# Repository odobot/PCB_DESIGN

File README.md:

# HALLO EYE

# LORA GATEWAY

# LORA TRACKER

# PENTASLAM BOARD V2
### Fixed issue of overheating that occured in V1.

# VEHICLE TELEMATICS

# PENTASLAM BOARD
### https://oshwlab.com/ndibapeter4/hexapod

# HEXAPOD BOARD
### https://oshwlab.com/ndibapeter4/hexapod

# SWIMMING-POOL-REGULATOR
### https://oshwlab.com/ndibapeter4/wsa-pcb

# CO2_SENSOR_BOARD

# NFC-READER FOR A TRAIN
### https://oshwlab.com/ndibapeter4/nfc-tag

# MOTOR-KIT BOARD
micro-ros motor control learning kit

24-08-22 at 06 37 44_fead27ea](https://github.com/user-attachments/assets/46265f90-ea3d-4042-9f53-f933ec7b34d7)

# ARDUINO-MEGA CUSTOM BOARD

# GREENHOUSE PCB

# ATMEGA32_ROBOT

# IR-ARRAY
used in line tracking robot

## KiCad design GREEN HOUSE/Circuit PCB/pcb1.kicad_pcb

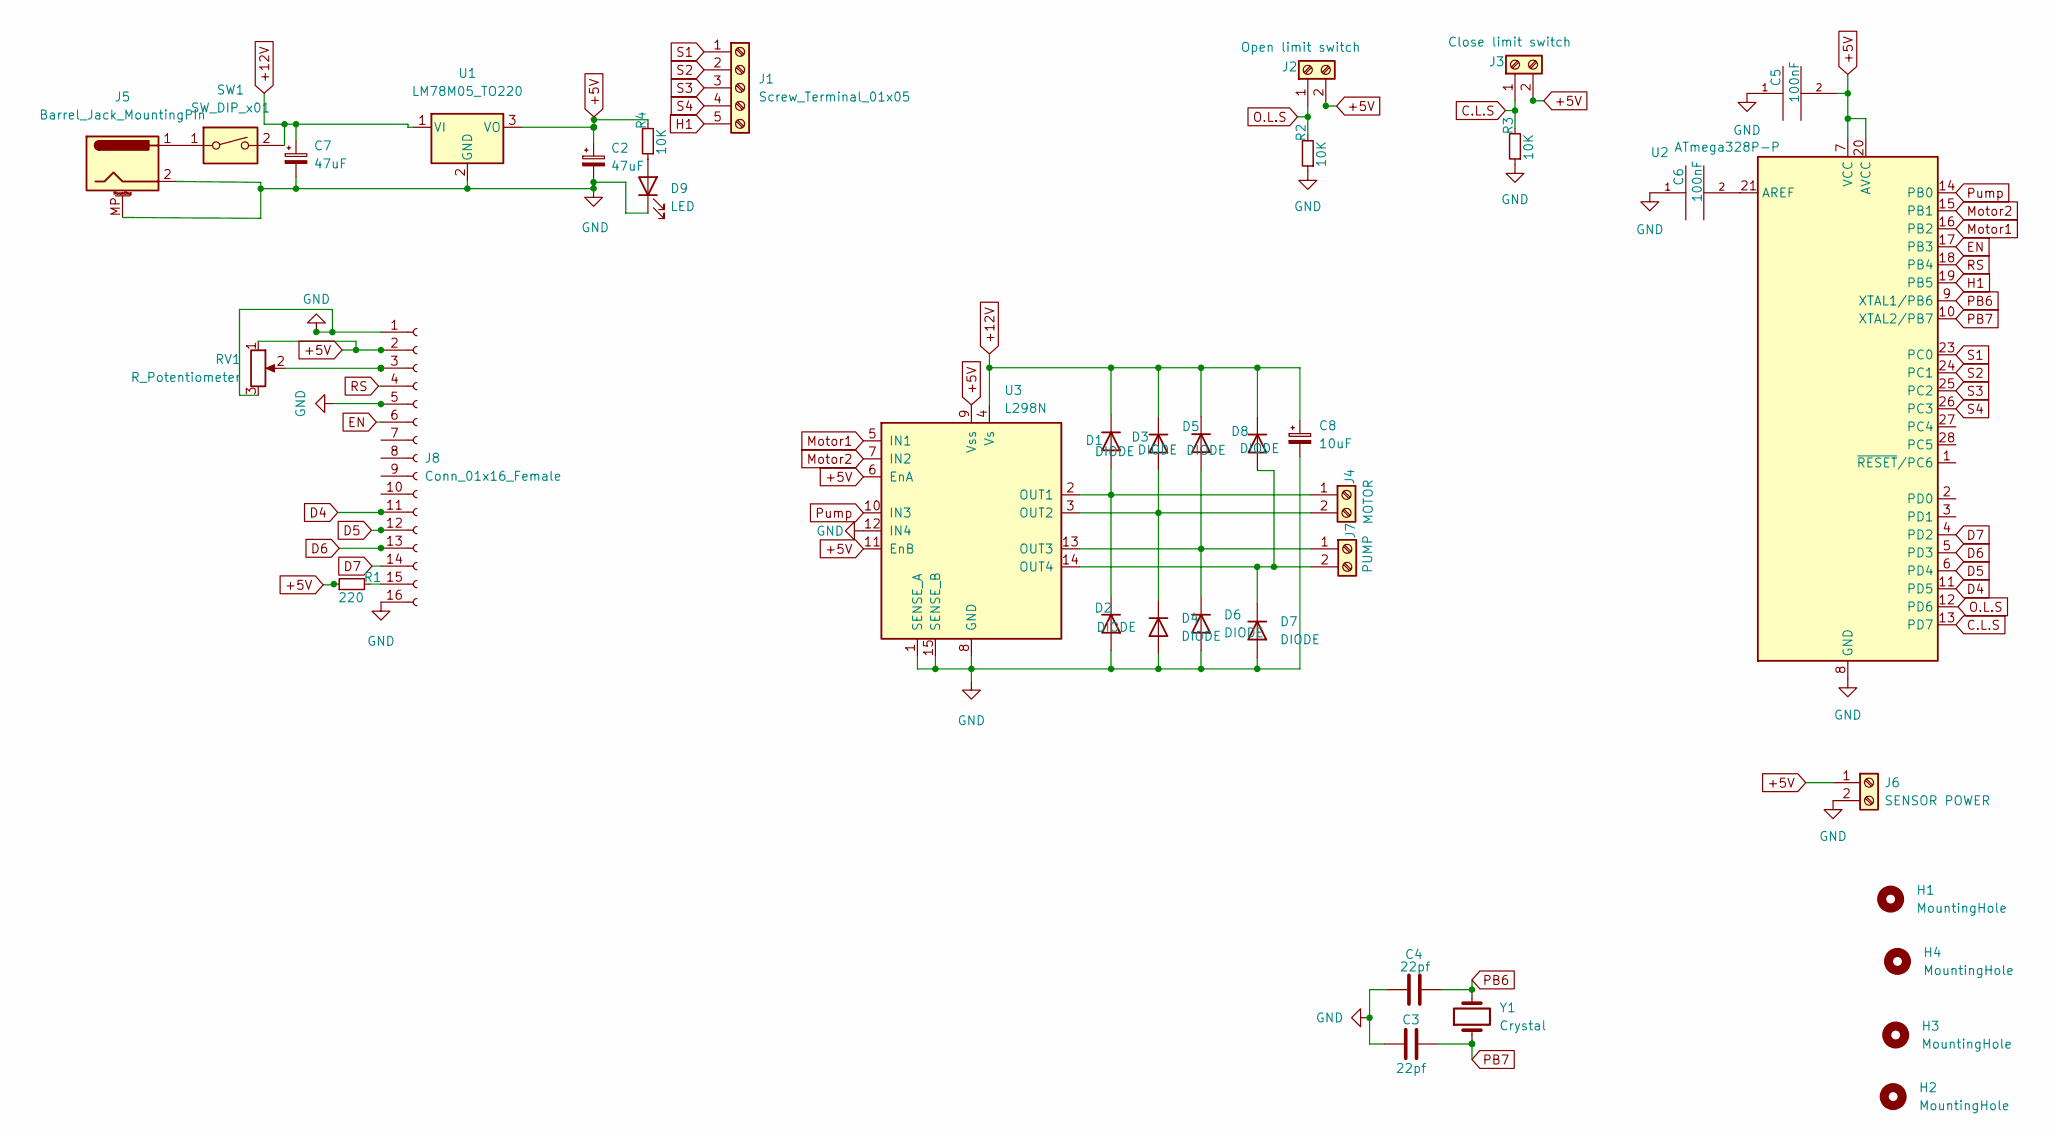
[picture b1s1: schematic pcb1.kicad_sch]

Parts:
C2, C7: 47uF; CP_Radial_D10.0mm_P5.00mm
C3, C4: 22pf; C_Disc_D3.4mm_W2.1mm_P2.50mm
C5, C6: 100nF; C_Disc_D3.0mm_W2.0mm_P2.50mm
C8: 10uF; CP_Radial_D10.0mm_P5.00mm
D1, D2, D3, D4, D5, D6, D7, D8: DIODE; D_A-405_P10.16mm_Horizontal
D9: LED; LED_D5.0mm
H1, H2, H3, H4: MountingHole; MountingHole_2.1mm
J1: Screw_Terminal_01x05; TerminalBlock_Phoenix_MKDS-1,5-5_1x05_P5.00mm_Horizontal
J2: Open limit switch; TerminalBlock_Phoenix_MKDS-1,5-2-5.08_1x02_P5.08mm_Horizont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
J3: Close limit switch; TerminalBlock_Phoenix_MKDS-1,5-2-5.08_1x02_P5.08mm_Horizont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
J4: MOTOR; TerminalBlock_Phoenix_MKDS-1,5-2-5.08_1x02_P5.08mm_Horizont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
J5: Barrel_Jack_MountingPin; BarrelJack_CUI_PJ-063AH_Horizontal
J6: SENSOR POWER; TerminalBlock_Phoenix_MKDS-1,5-2-5.08_1x02_P5.08mm_Horizont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
J7: PUMP; TerminalBlock_Phoenix_MKDS-1,5-2-5.08_1x02_P5.08mm_Horizont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
J8: Conn_01x16_Female; PinSocket_1x16_P2.54mm_Vertical
R1: 220; R_Axial_DIN0516_L15.5mm_D5.0mm_P20.32mm_Horizontal
R2, R3: 10K; R_Axial_DIN0516_L15.5mm_D5.0mm_P20.32mm_Horizontal
R4: 10K; R_Axial_DIN0516_L15.5mm_D5.0mm_P7.62mm_Vertical
RV1: R_Potentiometer; Potentiometer_Bourns_3296W_Vertical
SW1: SW_DIP_x01; SW_CuK_OS102011MA1QN1_SPDT_Angled
U1: LM78M05_TO220; TO-220-3_Vertical
U2: ATmega328P-P; DIP-28_W7.62mm
U3: L298N; TO-220-15_P2.54x2.54mm_StaggerOdd_Lead4.58mm_Vertical
Y1: Crystal; Crystal_HC49-4H_Vertical

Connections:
+5V: C2.1, C5.2, J2.2, J3.2, J6.1, J8.2, R1.1, R4.2, RV1.1, U1.3 (VO), U2.7 (VCC), U2.20 (AVCC), U3.6 (EnA), U3.9 (Vss), U3.11 (EnB)
+12V: C7.1, C8.1, D1.2 (K), D3.2 (K), D5.2 (K), D8.2 (K), SW1.2, U1.1 (VI), U3.4 (Vs)
C.L.S: J3.1, R3.2, U2.13 (PD7)
D4: J8.11, U2.11 (PD5)
D5: J8.12, U2.6 (PD4)
D6: J8.13, U2.5 (PD3)
D7: J8.14, U2.4 (PD2)
EN: J8.6, U2.17 (PB3)
GND: C2.2, C3.1, C4.1, C5.1, C6.1, C7.2, C8.2, D2.1 (A), D4.1 (A), D6.1 (A), D7.1 (A), D9.1 (K), J5.2, J5.MP (MountPin), J6.2, J8.1, J8.5, J8.16, R2.1, R3.1, RV1.3, U1.2 (GND), U2.8 (GND), U2.22 (GND), U3.1 (SENSE_A), U3.8 (GND), U3.12 (IN4), U3.15 (SENSE_B)
H1: J1.5, U2.19 (PB5)
Motor1: U2.16 (PB2), U3.5 (IN1)
Motor2: U2.15 (PB1), U3.7 (IN2)
unnamed: C6.2, U2.21 (AREF)
unnamed: D1.1 (A), D2.2 (K), J4.1, U3.2 (OUT1)
unnamed: D3.1 (A), D4.2 (K), J4.2, U3.3 (OUT2)
unnamed: D5.1 (A), D6.2 (K), J7.1, U3.13 (OUT3)
unnamed: D7.2 (K), D8.1 (A), J7.2, U3.14 (OUT4)
unnamed: D9.2 (A), R4.1
unnamed: J5.1, SW1.1
unnamed: J8.3, RV1.2
unnamed: J8.15, R1.2
O.L.S: J2.1, R2.2, U2.12 (PD6)
PB6: C4.2, U2.9 (XTAL1/PB6), Y1.2
PB7: C3.2, U2.10 (XTAL2/PB7), Y1.1
Pump: U2.14 (PB0), U3.10 (IN3)
RS: J8.4, U2.18 (PB4)
S1: J1.1, U2.23 (PC0)
S2: J1.2, U2.24 (PC1)
S3: J1.3, U2.25 (PC2)
S4: J1.4, U2.26 (PC3)

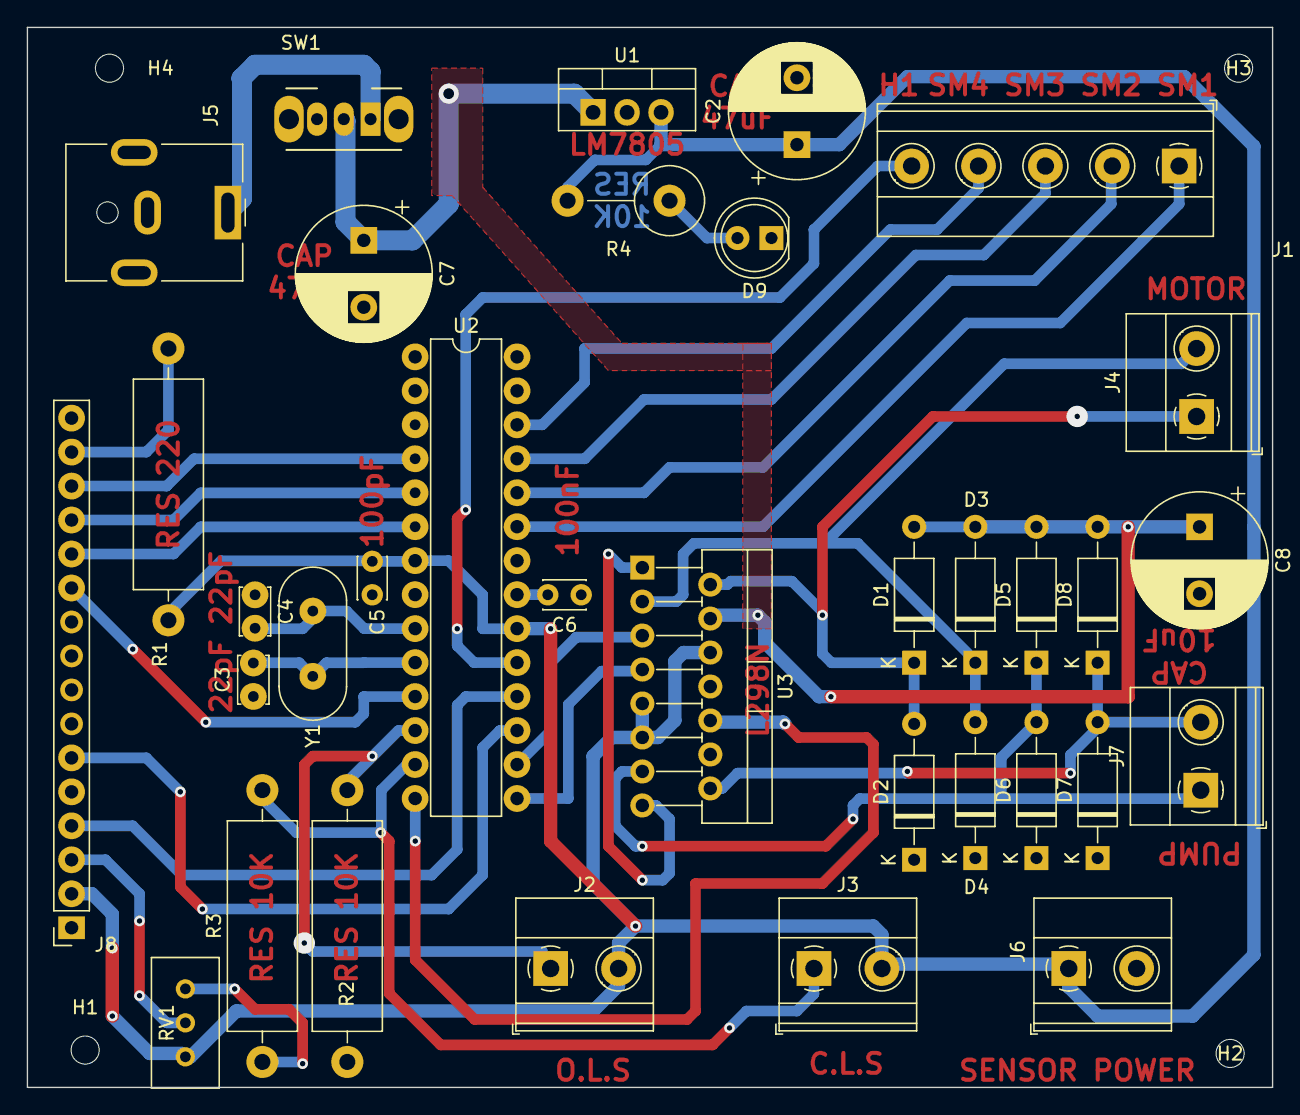
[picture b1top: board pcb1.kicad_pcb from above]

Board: 2 copper layers, 93.1 x 79.2 mm, 38 parts (0 on the bottom side), 30 nets.

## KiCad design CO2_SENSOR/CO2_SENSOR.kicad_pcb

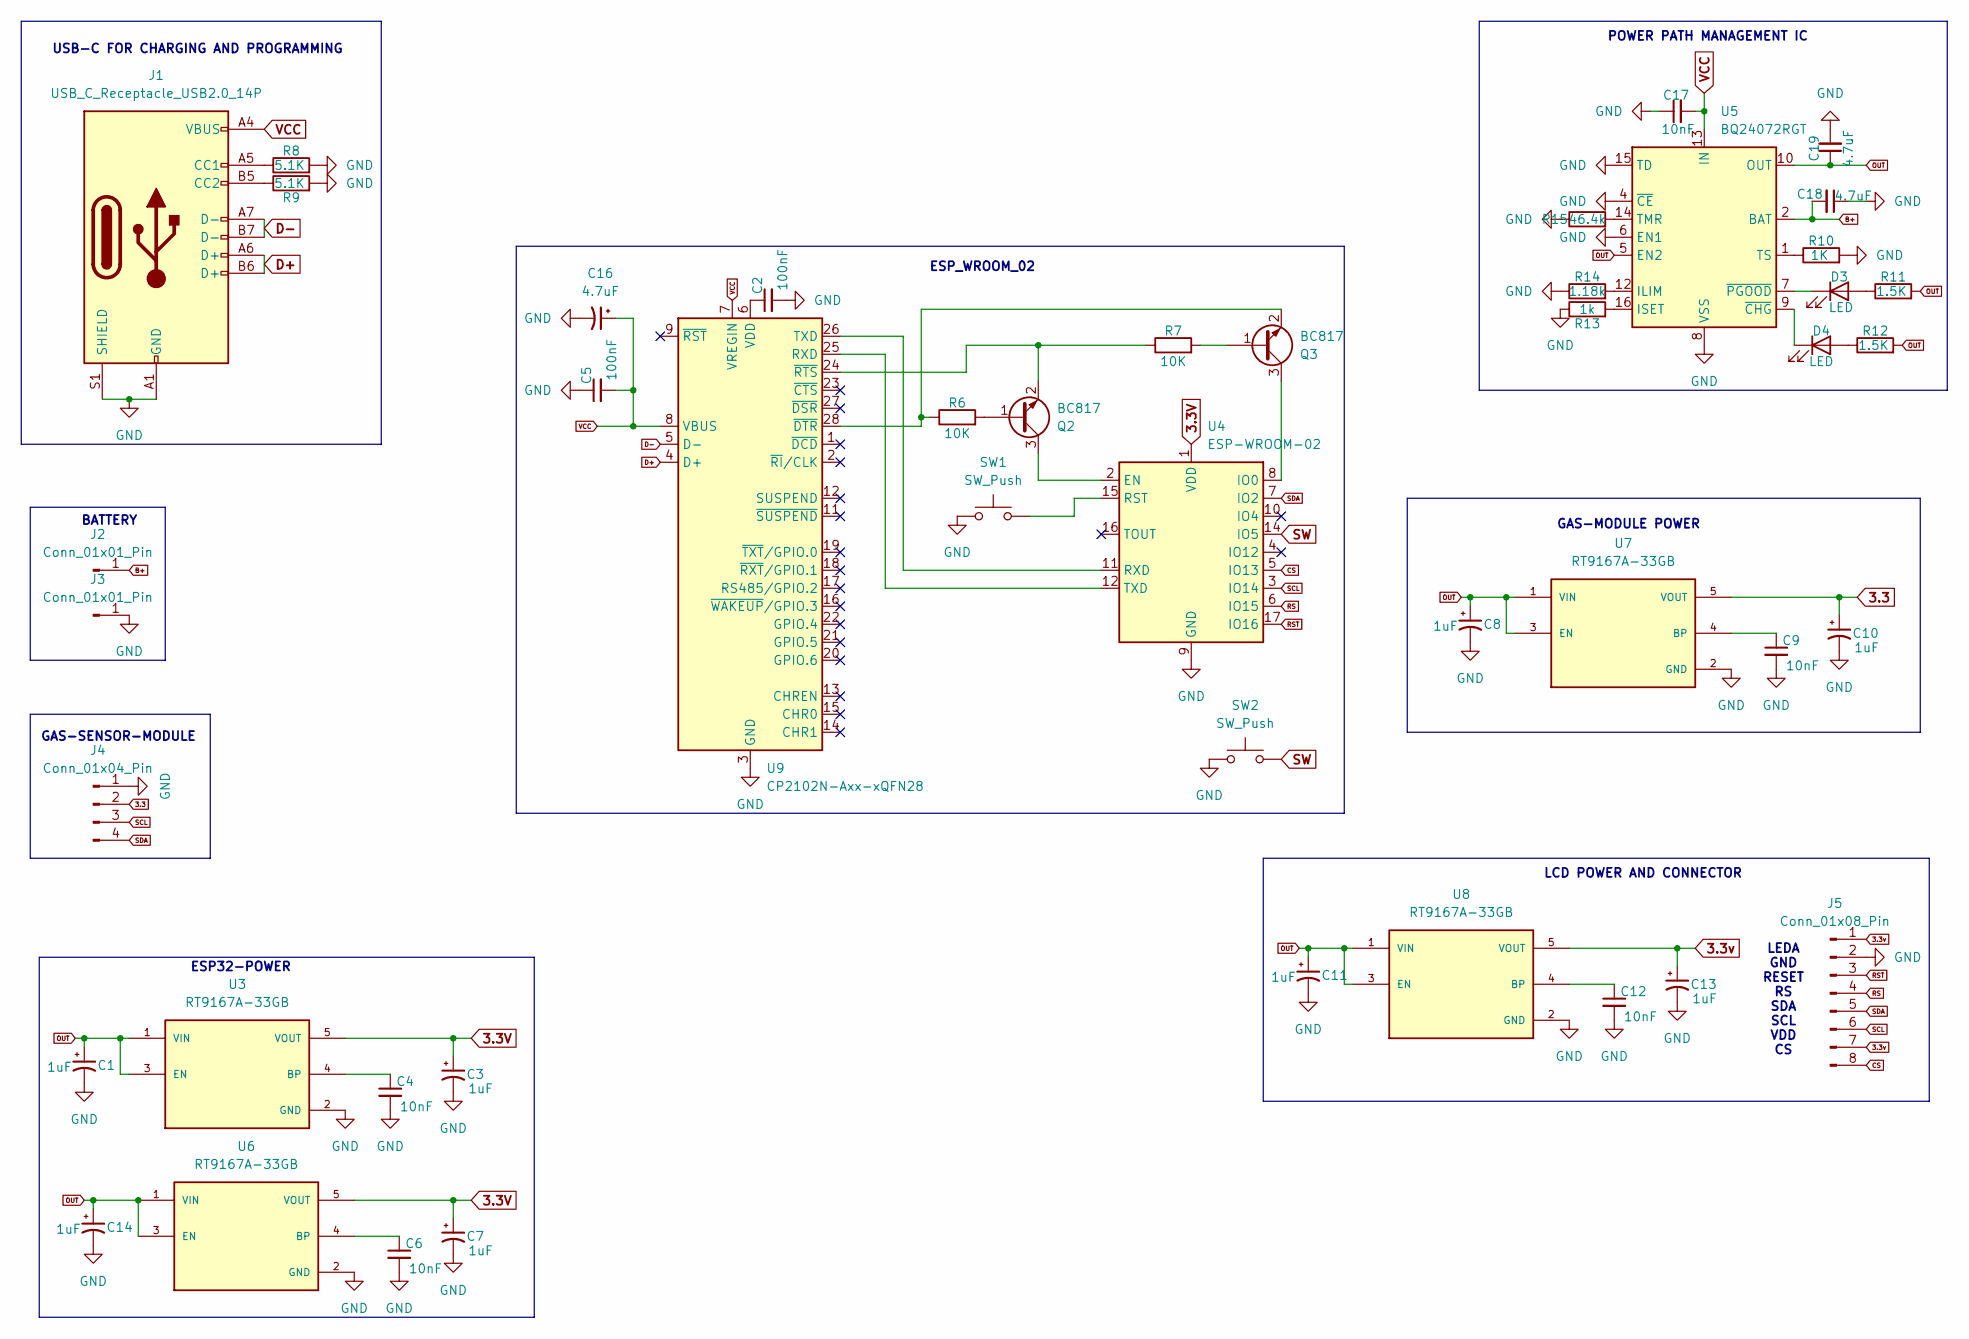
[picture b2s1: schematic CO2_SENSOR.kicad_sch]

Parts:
C1, C3, C7, C8, C10, C11, C13, C14: 1uF; CP_EIA-6032-20_AVX-F_Pad2.25x2.35mm_HandSolder
C2: 100nF; C_0402_1005Metric
C4, C6, C9, C12, C17: 10nF; C_0805_2012Metric
C5: 100nF; C_0603_1608Metric
C16: 4.7uF; CP_EIA-6032-20_AVX-F_Pad2.25x2.35mm_HandSolder
C18, C19: 4.7uF; C_0805_2012Metric
D3, D4: LED; LED_0805_2012Metric
J1: USB_C_Receptacle_USB2.0_14P; USB_C_Receptacle_GCT_USB4105-xx-A_16P_TopMnt_Horizontal
J2, J3: Conn_01x01_Pin; TestPoint_Pad_1.5x1.5mm
J4: Conn_01x04_Pin; PinHeader_1x04_P2.54mm_Vertical
J5: Conn_01x08_Pin; lcd
Q2, Q3: BC817; SOT-23
R6, R7: 10K; R_0805_2012Metric
R8, R9: 5.1K; R_0402_1005Metric
R10: 1K; R_0402_1005Metric
R11, R12: 1.5K; R_0805_2012Metric
R13: 1k; R_0402_1005Metric
R14: 1.18k; R_0402_1005Metric
R15: 46.4k; R_0402_1005Metric
SW1, SW2: SW_Push; SW_Tactile_SPST_NO_Straight_CK_PTS636Sx25SMTRLFS
U3, U6, U7, U8: RT9167A-33GB; SOT94P279X129-5N; PARTREV April 2011
U4: ESP-WROOM-02
U5: BQ24072RGT; VQFN-16-1EP_3x3mm_P0.5mm_EP1.6x1.6mm
U9: CP2102N-Axx-xQFN28; QFN-28-1EP_5x5mm_P0.5mm_EP3.35x3.35mm

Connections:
3.3: C10.1, J4.2, U7.5 (VOUT)
3.3V: C3.1, C7.1, U3.5 (VOUT), U4.1 (VDD), U6.5 (VOUT)
3.3v: C13.1, J5.1, J5.7, U8.5 (VOUT)
B+: C18.2, J2.1, U5.2 (BAT), U5.3 (BAT)
CS: J5.8, U4.5 (IO13)
D+: J1.A6 (D+), J1.B6 (D+), U9.4 (D+)
D-: J1.A7 (D-), J1.B7 (D-), U9.5 (D-)
GND: C1.2, C2.2, C3.2, C4.2, C5.1, C6.2, C7.2, C8.2, C9.2, C10.2, C11.2, C12.2, C13.2, C14.2, C16.2, C17.1, C18.1, C19.2, J1.A1 (GND), J1.A12 (GND), J1.B1 (GND), J1.B12 (GND), J1.S1 (SHIELD), J3.1, J4.1, J5.2, R8.2, R9.2, R10.2, R13.1, R14.1, R15.1, SW1.1, SW2.1, U3.2 (GND), U4.9 (GND), U4.13 (GND), U4.18 (GND), U4.19 (GND), U5.4 (~CE), U5.6 (EN1), U5.8 (VSS), U5.15 (TD), U5.17 (VSS), U6.2 (GND), U7.2 (GND), U8.2 (GND), U9.3 (GND), U9.29 (GND)
unnamed: D3.2 (A), R11.1
unnamed: D3.1 (K), U5.7 (~PGOOD)
unnamed: D4.2 (A), R12.1
unnamed: D4.1 (K), U5.9 (~CHG)
unnamed: J1.A5 (CC1), R8.1
unnamed: J1.B5 (CC2), R9.1
unnamed: Q2.1 (B), R6.2
unnamed: Q2.3 (C), U4.2 (EN)
unnamed: Q2.2 (E), R7.1, U9.24 (~RTS)
unnamed: Q3.1 (B), R7.2
unnamed: Q3.3 (C), U4.8 (IO0)
unnamed: Q3.2 (E), R6.1, U9.28 (~DTR)
unnamed: C4.1, U3.4 (BP)
unnamed: SW1.2, U4.15 (RST)
unnamed: U4.11 (RXD), U9.26 (TXD)
unnamed: U4.12 (TXD), U9.25 (RXD)
unnamed: R14.2, U5.12 (ILIM)
unnamed: R13.2, U5.16 (ISET)
unnamed: R15.2, U5.14 (TMR)
unnamed: R10.1, U5.1 (TS)
unnamed: C6.1, U6.4 (BP)
unnamed: C9.1, U7.4 (BP)
unnamed: C12.1, U8.4 (BP)
unnamed: C2.1, U9.6 (VDD)
OUT: C1.1, C8.1, C11.1, C14.1, C19.1, R11.2, R12.2, U3.1 (VIN), U3.3 (EN), U5.5 (EN2), U5.10 (OUT), U5.11 (OUT), U6.1 (VIN), U6.3 (EN), U7.1 (VIN), U7.3 (EN), U8.1 (VIN), U8.3 (EN)
RS: J5.4, U4.6 (IO15)
RST: J5.3, U4.17 (IO16)
SCL: J4.3, J5.6, U4.3 (IO14)
SDA: J4.4, J5.5, U4.7 (IO2)
SW: SW2.2, U4.14 (IO5)
VCC: C5.2, C16.1, C17.2, J1.A4 (VBUS), J1.A9 (VBUS), J1.B4 (VBUS), J1.B9 (VBUS), U5.13 (IN), U9.7 (VREGIN), U9.8 (VBUS)

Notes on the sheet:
GAS-SENSOR-MODULE
BATTERY
LEDA GND RESET RS SDA SCL VDD CS
POWER PATH MANAGEMENT IC
GAS-MODULE POWER
LCD POWER AND CONNECTOR
ESP32-POWER
USB-C FOR CHARGING AND PROGRAMMING
ESP_WROOM_02

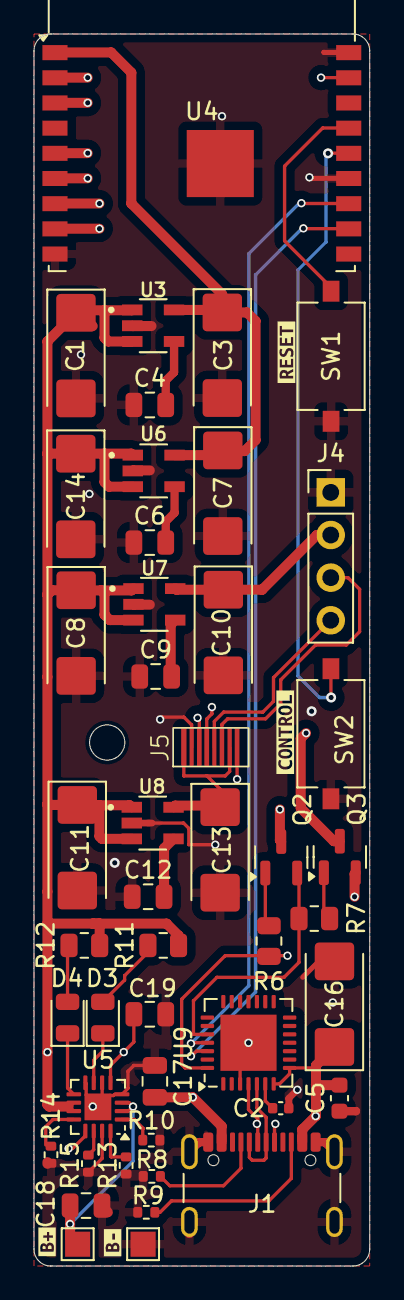
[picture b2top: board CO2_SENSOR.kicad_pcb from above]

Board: 4 copper layers, 20.0 x 73.4 mm, 50 parts (0 on the bottom side), 39 nets.

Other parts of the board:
kibuzzard-66E83A4A: G***; kibuzzard-66E83A4A
kibuzzard-66E83A64: G***; kibuzzard-66E83A64
kibuzzard-66E824C4: G***; kibuzzard-66E824C4
kibuzzard-66E82444: G***; kibuzzard-66E82444

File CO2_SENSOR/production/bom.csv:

Designator,Footprint,Quantity,Value,LCSC Part #,
"C1, C10, C11, C13, C14, C3, C7, C8",CP_EIA-6032-20_AVX-F_Pad2.25x2.35mm_HandSolder,8,1uF,C5673,
"C12, C17, C4, C6, C9",805,5,10nF,C519911,
C16,CP_EIA-6032-20_AVX-F_Pad2.25x2.35mm_HandSolder,1,4.7uF,C1953079,
"C18, C19",805,2,4.7uF,C913642,
C2,402,1,100nF,C309458,
C5,603,1,100nF,C519438,
"D3, D4",805,2,LED,C397047,
J1,USB_C_Receptacle_GCT_USB4105-xx-A_16P_TopMnt_Horizontal,1,USB_C_Receptacle_USB2.0_14P,C309343,
J4,PinHeader_1x04_P2.54mm_Vertical,1,Conn_01x04_Pin,C7501582,
"Q2, Q3",SOT-23,2,BC817,C39828,
"R10, R13",402,2,1K,C100195,
"R11, R12",805,2,1.5K,C269739,
R14,402,1,1.18k,C3016052,
R15,402,1,46.4k,C52378,
"R6, R7",805,2,10K,C60490,
"R8, R9",402,2,5.1K,C325524,
"SW1, SW2",SW_Tactile_SPST_NO_Straight_CK_PTS636Sx25SMTRLFS,2,SW_Push,C2689642,
"U3, U6, U7, U8",SOT94P279X129-5N,4,RT9167A-33GB,C113513,
U4,ESP-WROOM-02,1,ESP-WROOM-02,C81770,
U5,VQFN-16-1EP_3x3mm_P0.5mm_EP1.6x1.6mm,1,BQ24072RGT,C140288,
U9,QFN-28-1EP_5x5mm_P0.5mm_EP3.35x3.35mm,1,CP2102N-Axx-xQFN28,C964632,

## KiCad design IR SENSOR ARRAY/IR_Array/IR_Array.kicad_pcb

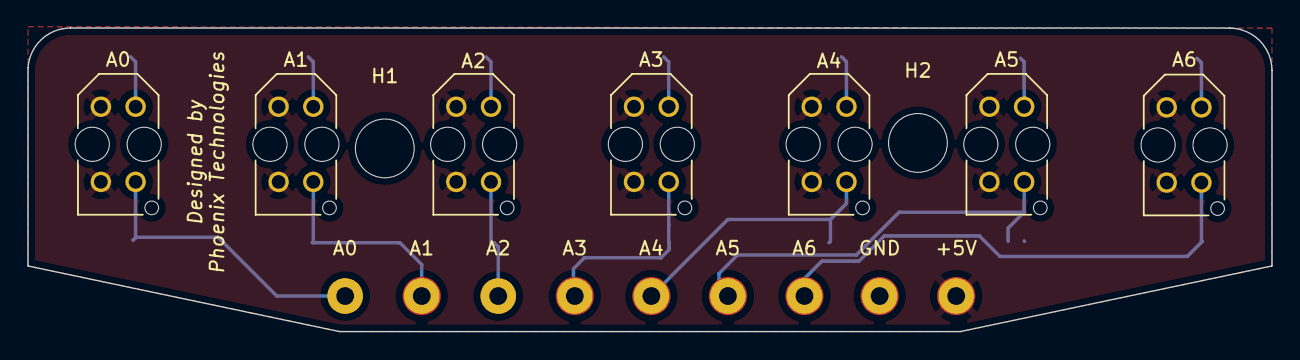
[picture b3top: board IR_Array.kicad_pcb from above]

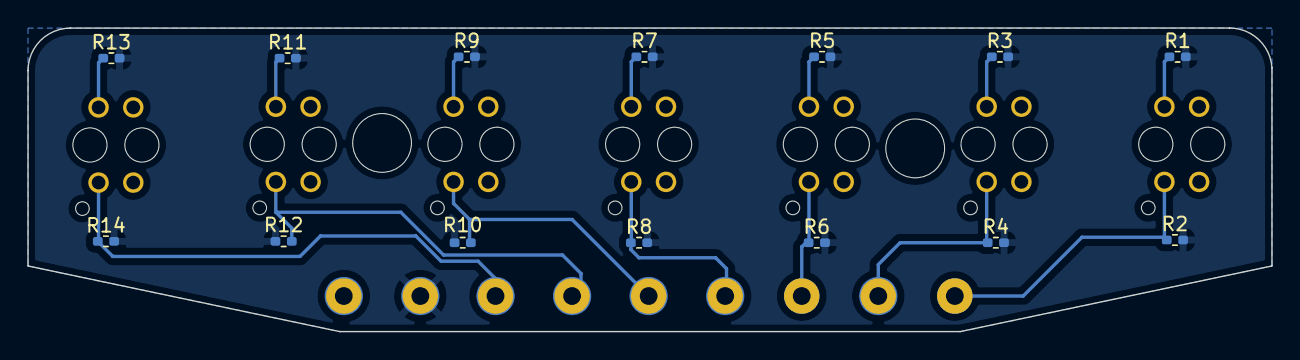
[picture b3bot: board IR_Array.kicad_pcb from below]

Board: 2 copper layers, 91.0 x 22.2 mm, 32 parts (14 on the bottom side), 9 nets.

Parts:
+5V: MountingHole_Pad; MountingHole_2.5mm_Pad_TopBottom
A0, A1#2, A2#2, A3#2, A4#2, A5#2, A6#2: TCRT5000; OPTO_TCRT5000
A0#2, A1, A2, A3, A4, A5, A6: MountingHole_Pad; MountingHole_2.5mm_Pad_TopBottom
GND: MountingHole_Pad; MountingHole_2.5mm_Pad_TopBottom
H1, H2: MountingHole; MountingHole_4.3mm_M4
R1, R3, R5, R7, R9, R11, R13: 220; R_0402_1005Metric_Pad0.72x0.64mm_HandSolder
R2, R4, R6, R8, R10, R12, R14: 10k; R_0402_1005Metric_Pad0.72x0.64mm_HandSolder

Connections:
+5V: +5V.1, A0.A, A0.COLL, A1#2.A, A1#2.COLL, A2#2.A, A2#2.COLL, A3#2.A, A3#2.COLL, A4#2.A, A4#2.COLL, A5#2.A, A5#2.COLL, A6#2.A, A6#2.COLL
A0: A0.E, A0#2.1, R2.1
A1: A1.1, A1#2.E, R4.1
A2: A2.1, A2#2.E, R6.1
A3: A3.1, A3#2.E, R8.1
A4: A4.1, A4#2.E, R10.1
A5: A5.1, A5#2.E, R12.1
A6: A6.1, A6#2.E, R14.1
Earth: GND.1, R1.2, R2.2, R3.2, R4.2, R5.2, R6.2, R7.2, R8.2, R9.2, R10.2, R11.2, R12.2, R13.2, R14.2

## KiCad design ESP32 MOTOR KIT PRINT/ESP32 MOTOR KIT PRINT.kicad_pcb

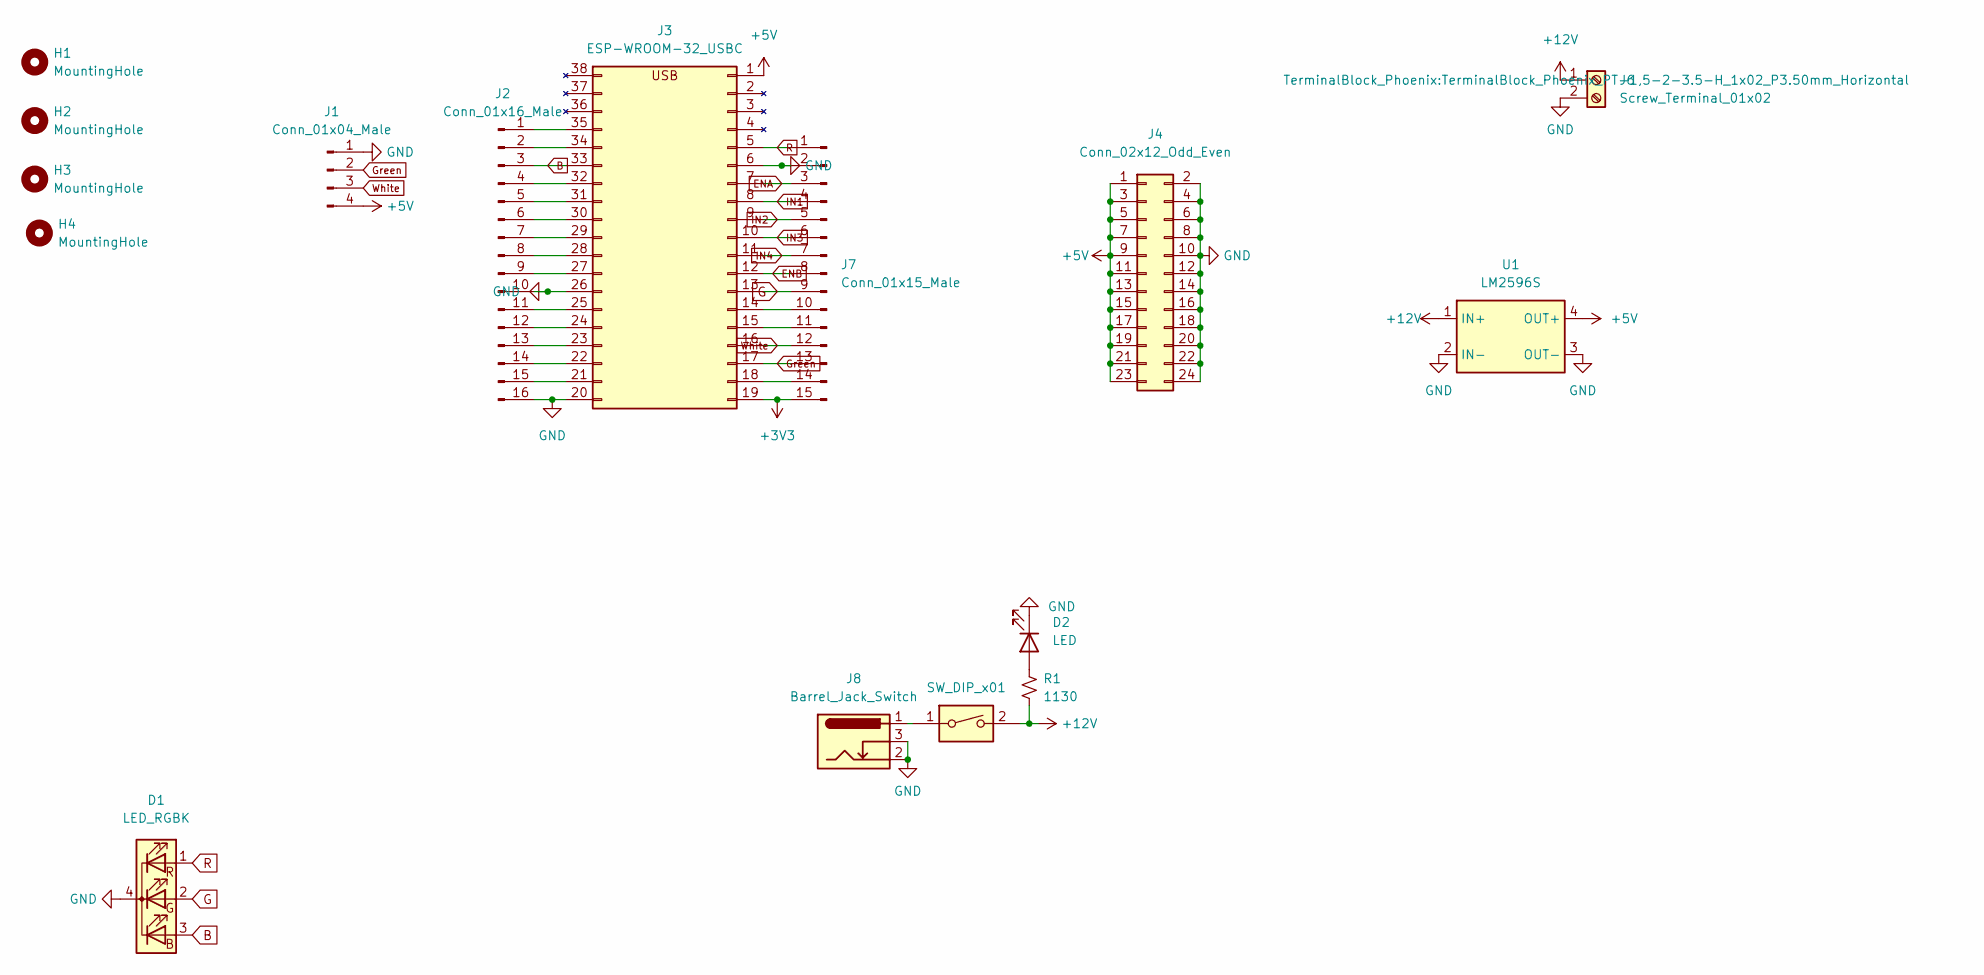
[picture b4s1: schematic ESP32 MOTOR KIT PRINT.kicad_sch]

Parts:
D1: LED_RGBK; LED_D5.0mm-4_RGB
D2: LED; LED_D3.0mm
H1, H2, H3, H4: MountingHole; MountingHole_2.5mm
J1: Conn_01x04_Male; JST_XH_B4B-XH-A_1x04_P2.50mm_Vertical
J2: Conn_01x16_Male; PinHeader_1x16_P2.54mm_Vertical
J3: ESP-WROOM-32_USBC; ESP-WROOM-32 TYPE C
J4: Conn_02x12_Odd_Even; PinHeader_2x12_P2.54mm_Vertical
J6: Screw_Terminal_01x02; TerminalBlock_Phoenix_PT-1,5-2-3.5-H_1x02_P3.50mm_Horizontal
J7: Conn_01x15_Male; PinHeader_1x15_P2.54mm_Vertical
J8: Barrel_Jack_Switch; BarrelJack_Wuerth_6941xx301002
R1: 1130; R_Axial_DIN0204_L3.6mm_D1.6mm_P1.90mm_Vertical
SW1: SW_DIP_x01; SW_E-Switch_EG1224_SPDT_Angled
U1: LM2596S; LM2596

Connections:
+3V3: J3.19 (3V3), J7.15
+5V: J1.4, J3.1 (5V), J4.1, J4.3, J4.5, J4.7, J4.9, J4.11, J4.13, J4.15, J4.17, J4.19, J4.21, J4.23, U1.4 (OUT+)
+12V: J6.1, R1.2, SW1.2, U1.1 (IN+)
B: D1.3 (BA), J2.3, J3.33 (P0)
ENA: J3.7 (P12), J7.3
ENB: J3.12 (P33), J7.8
G: D1.2 (GA), J3.13 (P32), J7.9
GND: D1.4 (K), D2.1 (K), J1.1, J2.10, J2.16, J3.6 (GND), J3.20 (GND), J3.26 (GND), J4.2, J4.4, J4.6, J4.8, J4.10, J4.12, J4.14, J4.16, J4.18, J4.20, J4.22, J4.24, J6.2, J7.2, J8.2, J8.3, U1.2 (IN-), U1.3 (OUT-)
Green: J1.2, J3.17 (P36/SVP), J7.13
IN1: J3.8 (P14), J7.4
IN2: J3.9 (P27), J7.5
IN3: J3.10 (P26), J7.6
IN4: J3.11 (P25), J7.7
unnamed: D2.2 (A), R1.1
unnamed: J2.1, J3.35 (P15)
unnamed: J2.2, J3.34 (P2)
unnamed: J2.4, J3.32 (P4)
unnamed: J2.5, J3.31 (P16/RX2)
unnamed: J2.6, J3.30 (P17/TX2)
unnamed: J2.7, J3.29 (P5)
unnamed: J2.8, J3.28 (P18)
unnamed: J2.9, J3.27 (P19)
unnamed: J2.11, J3.25 (P21)
unnamed: J2.12, J3.24 (P3/RX0)
unnamed: J2.13, J3.23 (P1/TX0)
unnamed: J2.14, J3.22
unnamed: J2.15, J3.21 (P23)
unnamed: J3.14 (P35), J7.10
unnamed: J3.15 (P34), J7.11
unnamed: J3.18 (EN), J7.14
unnamed: J8.1, SW1.1
R: D1.1 (RA), J3.5 (P13), J7.1
White: J1.3, J3.16 (P39/SVN), J7.12

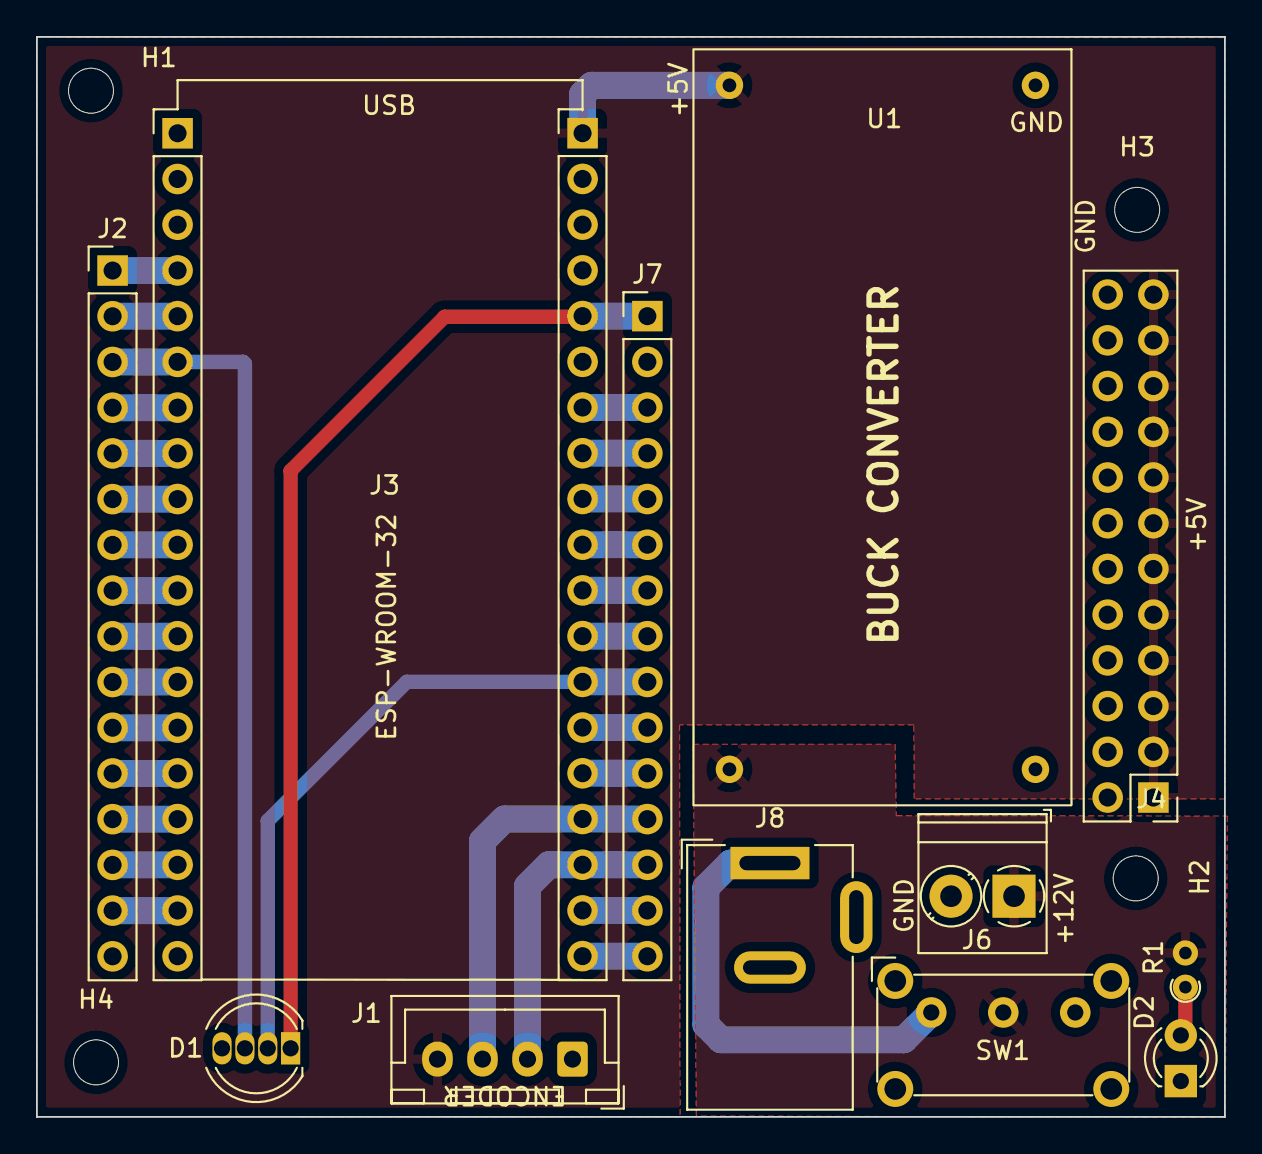
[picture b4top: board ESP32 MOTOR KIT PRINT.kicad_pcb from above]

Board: 2 copper layers, 66.0 x 60.0 mm, 16 parts (0 on the bottom side), 33 nets.

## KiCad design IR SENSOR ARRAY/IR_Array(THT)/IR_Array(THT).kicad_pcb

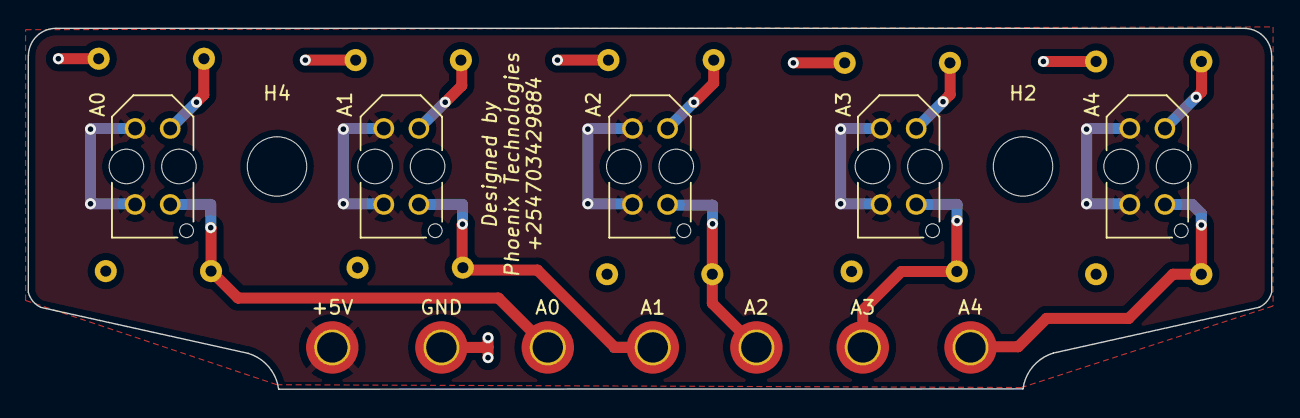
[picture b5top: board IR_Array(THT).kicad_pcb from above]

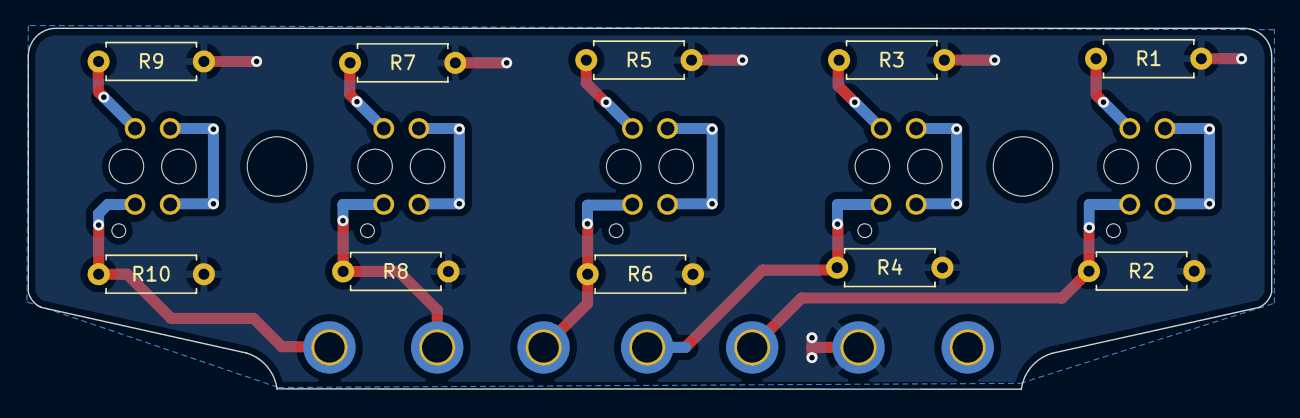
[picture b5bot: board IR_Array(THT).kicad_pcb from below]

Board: 2 copper layers, 90.0 x 26.1 mm, 24 parts (10 on the bottom side), 12 nets.

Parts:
+5V: MountingHole_Pad; MountingHole_2.2mm_M2_DIN965_Pad_TopBottom
A0, A1#2, A2#2, A3#2, A4#2: MountingHole_Pad; MountingHole_2.2mm_M2_DIN965_Pad_TopBottom
A0#2, A1, A2, A3, A4: TCRT5000; OPTO_TCRT5000
GND: MountingHole_Pad; MountingHole_2.2mm_M2_DIN965_Pad_TopBottom
H2, H4: MountingHole; MountingHole_4.3mm_M4
R1, R3, R5, R7, R9: 220; R_Axial_DIN0207_L6.3mm_D2.5mm_P7.62mm_Horizontal
R2, R4, R6, R8, R10: 10k; R_Axial_DIN0207_L6.3mm_D2.5mm_P7.62mm_Horizontal

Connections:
+5V: +5V.1, A0#2.A, A0#2.COLL, A1.A, A1.COLL, A2.A, A2.COLL, A3.A, A3.COLL, A4.A, A4.COLL
A0: A0.1, A0#2.E, R2.1
A1: A1.E, A1#2.1, R4.1
A2: A2.E, A2#2.1, R6.1
A3: A3.E, A3#2.1, R8.1
A4: A4.E, A4#2.1, R10.1
Earth: GND.1, R1.2, R2.2, R3.2, R4.2, R5.2, R6.2, R7.2, R8.2, R9.2, R10.2
unnamed: A0#2.CATH, R1.1
unnamed: A1.CATH, R3.1
unnamed: A2.CATH, R5.1
unnamed: A3.CATH, R7.1
unnamed: A4.CATH, R9.1

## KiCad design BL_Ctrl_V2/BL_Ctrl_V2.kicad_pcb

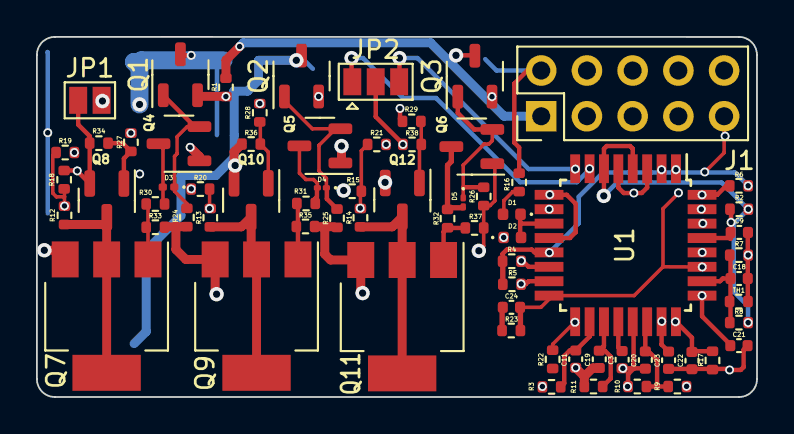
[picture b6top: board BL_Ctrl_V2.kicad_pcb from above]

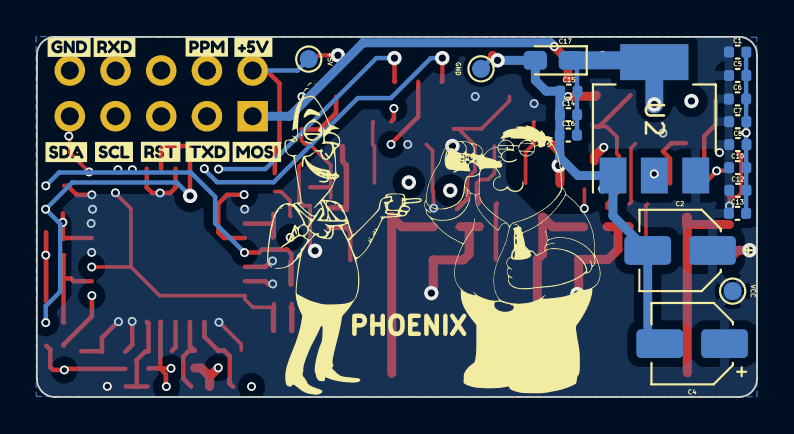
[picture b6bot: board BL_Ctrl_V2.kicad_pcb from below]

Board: 4 copper layers, 40.0 x 20.0 mm, 98 parts (28 on the bottom side), 46 nets.

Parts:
+5V: TestPoint; TestPoint_Pad_D1.0mm
C1, C3, C8, C9, C11, C14, C15, C16, C18, C19, C20: 100nF; C_0402_1005Metric
C2, C4: 330uF 16V; CP_Elec_4x3
C5, C6, C7, C12, C13: C_0402_1005Metric
C10: uF 25V; C_0402_1005Metric
C17: C_Polarized_Small; CP_EIA-2012-15_AVX-P_Pad1.30x1.05mm_HandSolder
C21, C22, C23: 100nf; C_0402_1005Metric
C24: 1nf; C_0402_1005Metric
D1, D2: LED; LED_0402_1005Metric
D3: 1N4003; D_0201_0603Metric
D4, D5: 1N4003; D_01005_0402Metric
GND: TestPoint; TestPoint_Pad_D1.0mm
J1: Conn_02x05_Odd_Even; PinHeader_2x05_P2.54mm_Vertical
JP1: SolderJumper_2_Open; SolderJumper-2_P1.3mm_Open_Pad1.0x1.5mm
JP2: SolderJumper_3_Open; SolderJumper-3_P1.3mm_Open_Pad1.0x1.5mm
PHOENIX: LOGO; cheech2
Q1, Q2, Q3, Q4, Q5, Q6: BC547; SOT-23-3
Q7, Q9, Q11: ZXMP4A16G; SOT-223-3_TabPin2
Q8, Q10, Q12: BS870; SOT-23
R1, R9, R10, R11: 680R; R_0402_1005Metric
R2, R4, R5, R6: 1.8k; R_0402_1005Metric
R3, R30, R31, R32: 10R; R_0402_1005Metric
R7: 47k; R_0402_1005Metric
R8, R33, R34, R35, R36, R37, R38: 18k; R_0402_1005Metric
R12, R13, R14, R19, R20, R21: 4k7; R_0402_1005Metric
R15, R17, R18: R; R_0402_1005Metric
R16, R24, R25, R26: 1k8; R_0402_1005Metric
R22, R23: 27R; R_0402_1005Metric
R27, R28, R29: 100R; R_0402_1005Metric
TH1: Thermistor; R_0402_1005Metric
U1: ATmega168-20A; TQFP-32_7x7mm_P0.8mm
U2: AMS1117-5.0; SOT-223-3_TabPin2
VCC: TestPoint; TestPoint_Pad_D1.0mm
kibuzzard-65CCF6C9: G***; kibuzzard-65CCF6C9
kibuzzard-65CCF7AB: G***; kibuzzard-65CCF7AB
kibuzzard-65CCF7CE: G***; kibuzzard-65CCF7CE
kibuzzard-65CCF7FA: G***; kibuzzard-65CCF7FA
kibuzzard-65CCF70D: G***; kibuzzard-65CCF70D
kibuzzard-65CCF73D: G***; kibuzzard-65CCF73D
kibuzzard-65CCF654: G***; kibuzzard-65CCF654
kibuzzard-65CCF679: G***; kibuzzard-65CCF679
kibuzzard-65CDD6A5: G***; kibuzzard-65CDD6A5

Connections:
+5V: +5V.1, C14.1, C15.1, C16.1, C17.1, J1.2, R2.1, R3.2, R8.1, R16.1, U1.4 (VCC), U1.6 (VCC), U2.2 (VO)
/ADR1: JP2.1 (A), U1.7 (XTAL1/PB6)
/ADR2: JP2.3 (B), U1.8 (XTAL2/PB7)
/LED: D1.1 (K), D2.2 (A), U1.11 (PD7)
/MITTEL: R19.2, R20.2, R21.2, U1.10 (PD6)
/MOSI: J1.1, R1.1
/NULL_A: C23.2, R12.2, R18.2, R19.1, U1.23 (PC0)
/NULL_B: C22.2, R13.2, R17.1, R20.1, U1.24 (PC1)
/NULL_C: C21.2, R14.2, R15.2, R21.1, U1.25 (PC2)
/PHASE_A: Q7.2 (D), Q8.3 (D), R12.1
/PHASE_B: Q9.2 (D), Q10.3 (D), R13.1
/PHASE_C: Q11.2 (D), Q12.3 (D), R14.1
/PPM&ADR3: J1.4, JP1.2 (B)
/RESET: C9.1, J1.5, R2.2, U1.29 (~RESET/PC6)
/RXD: J1.8, U1.30 (PD0)
/SCL: J1.7, R22.2, U1.17 (PB5), U1.28 (PC5)
/SDA: C24.1, J1.9, R23.2, U1.16 (PB4), U1.27 (PC4)
/STEUER_A+: Q1.2 (B), R1.2, R5.1, U1.15 (PB3)
/STEUER_A-: R27.1, U1.1 (PD3)
/STEUER_B+: Q2.2 (B), R4.2, U1.14 (PB2)
/STEUER_B-: R28.1, U1.2 (PD4)
/STEUER_C+: Q3.2 (B), R6.1, U1.32 (PD2)
/STEUER_C-: R29.1, U1.9 (PD5), U1.12 (PB0)
/STROM: C19.1, R11.1, U1.19 (ADC6)
/TEMPERATUR: C18.1, R7.1, R8.2, TH1.1, U1.26 (PC3)
/TXD: J1.3, U1.31 (PD1)
/U_BAT: C20.1, R9.2, R10.1, U1.22 (ADC7)
GND: C1.2, C2.2, C3.2, C4.2, C5.2, C6.2, C7.2, C8.2, C9.2, C10.2, C11.2, C12.2, C13.2, C14.2, C15.2, C16.2, C17.2, C18.2, C19.2, C20.2, C21.1, C22.1, C23.1, D2.1 (K), GND.1, J1.10, JP1.1 (A), JP2.2 (C), Q1.3 (E), Q2.3 (E), Q3.3 (E), Q8.2 (S), Q10.2 (S), Q12.2 (S), R7.2, R10.2, R11.2, R15.1, R17.2, R18.1, R34.2, R36.2, R38.2, TH1.2, U1.3 (GND), U1.5 (GND), U1.21 (GND), U2.1 (GND)
unnamed: C24.2, R23.1
unnamed: D1.2 (A), R16.2
unnamed: D3.2 (A), Q4.3 (E), R30.1
unnamed: D3.1 (K), Q1.1 (C), Q4.2 (B), R24.2
unnamed: D4.2 (A), Q5.3 (E), R31.1
unnamed: D4.1 (K), Q2.1 (C), Q5.2 (B), R25.2
unnamed: D5.2 (A), Q6.3 (E), R32.1
unnamed: D5.1 (K), Q3.1 (C), Q6.2 (B), R26.2
unnamed: Q7.1 (G), R30.2, R33.1
unnamed: Q8.1 (G), R27.2, R34.1
unnamed: Q9.1 (G), R31.2, R35.1
unnamed: Q10.1 (G), R28.2, R36.1
unnamed: Q11.1 (G), R32.2, R37.1
unnamed: Q12.1 (G), R29.2, R38.1
unnamed: C3.1, U1.20 (AREF)
unnamed: C11.1, R3.1, U1.18 (AVCC)
unnamed: R4.1, R5.2, R6.2, U1.13 (PB1)
VCC: C1.1, C2.1, C4.1, C5.1, C6.1, C7.1, C8.1, C10.1, C12.1, C13.1, Q4.1 (C), Q5.1 (C), Q6.1 (C), Q7.3 (S), Q9.3 (S), Q11.3 (S), R9.1, R24.1, R25.1, R26.1, R33.2, R35.2, R37.2, U2.3 (VI), VCC.1
